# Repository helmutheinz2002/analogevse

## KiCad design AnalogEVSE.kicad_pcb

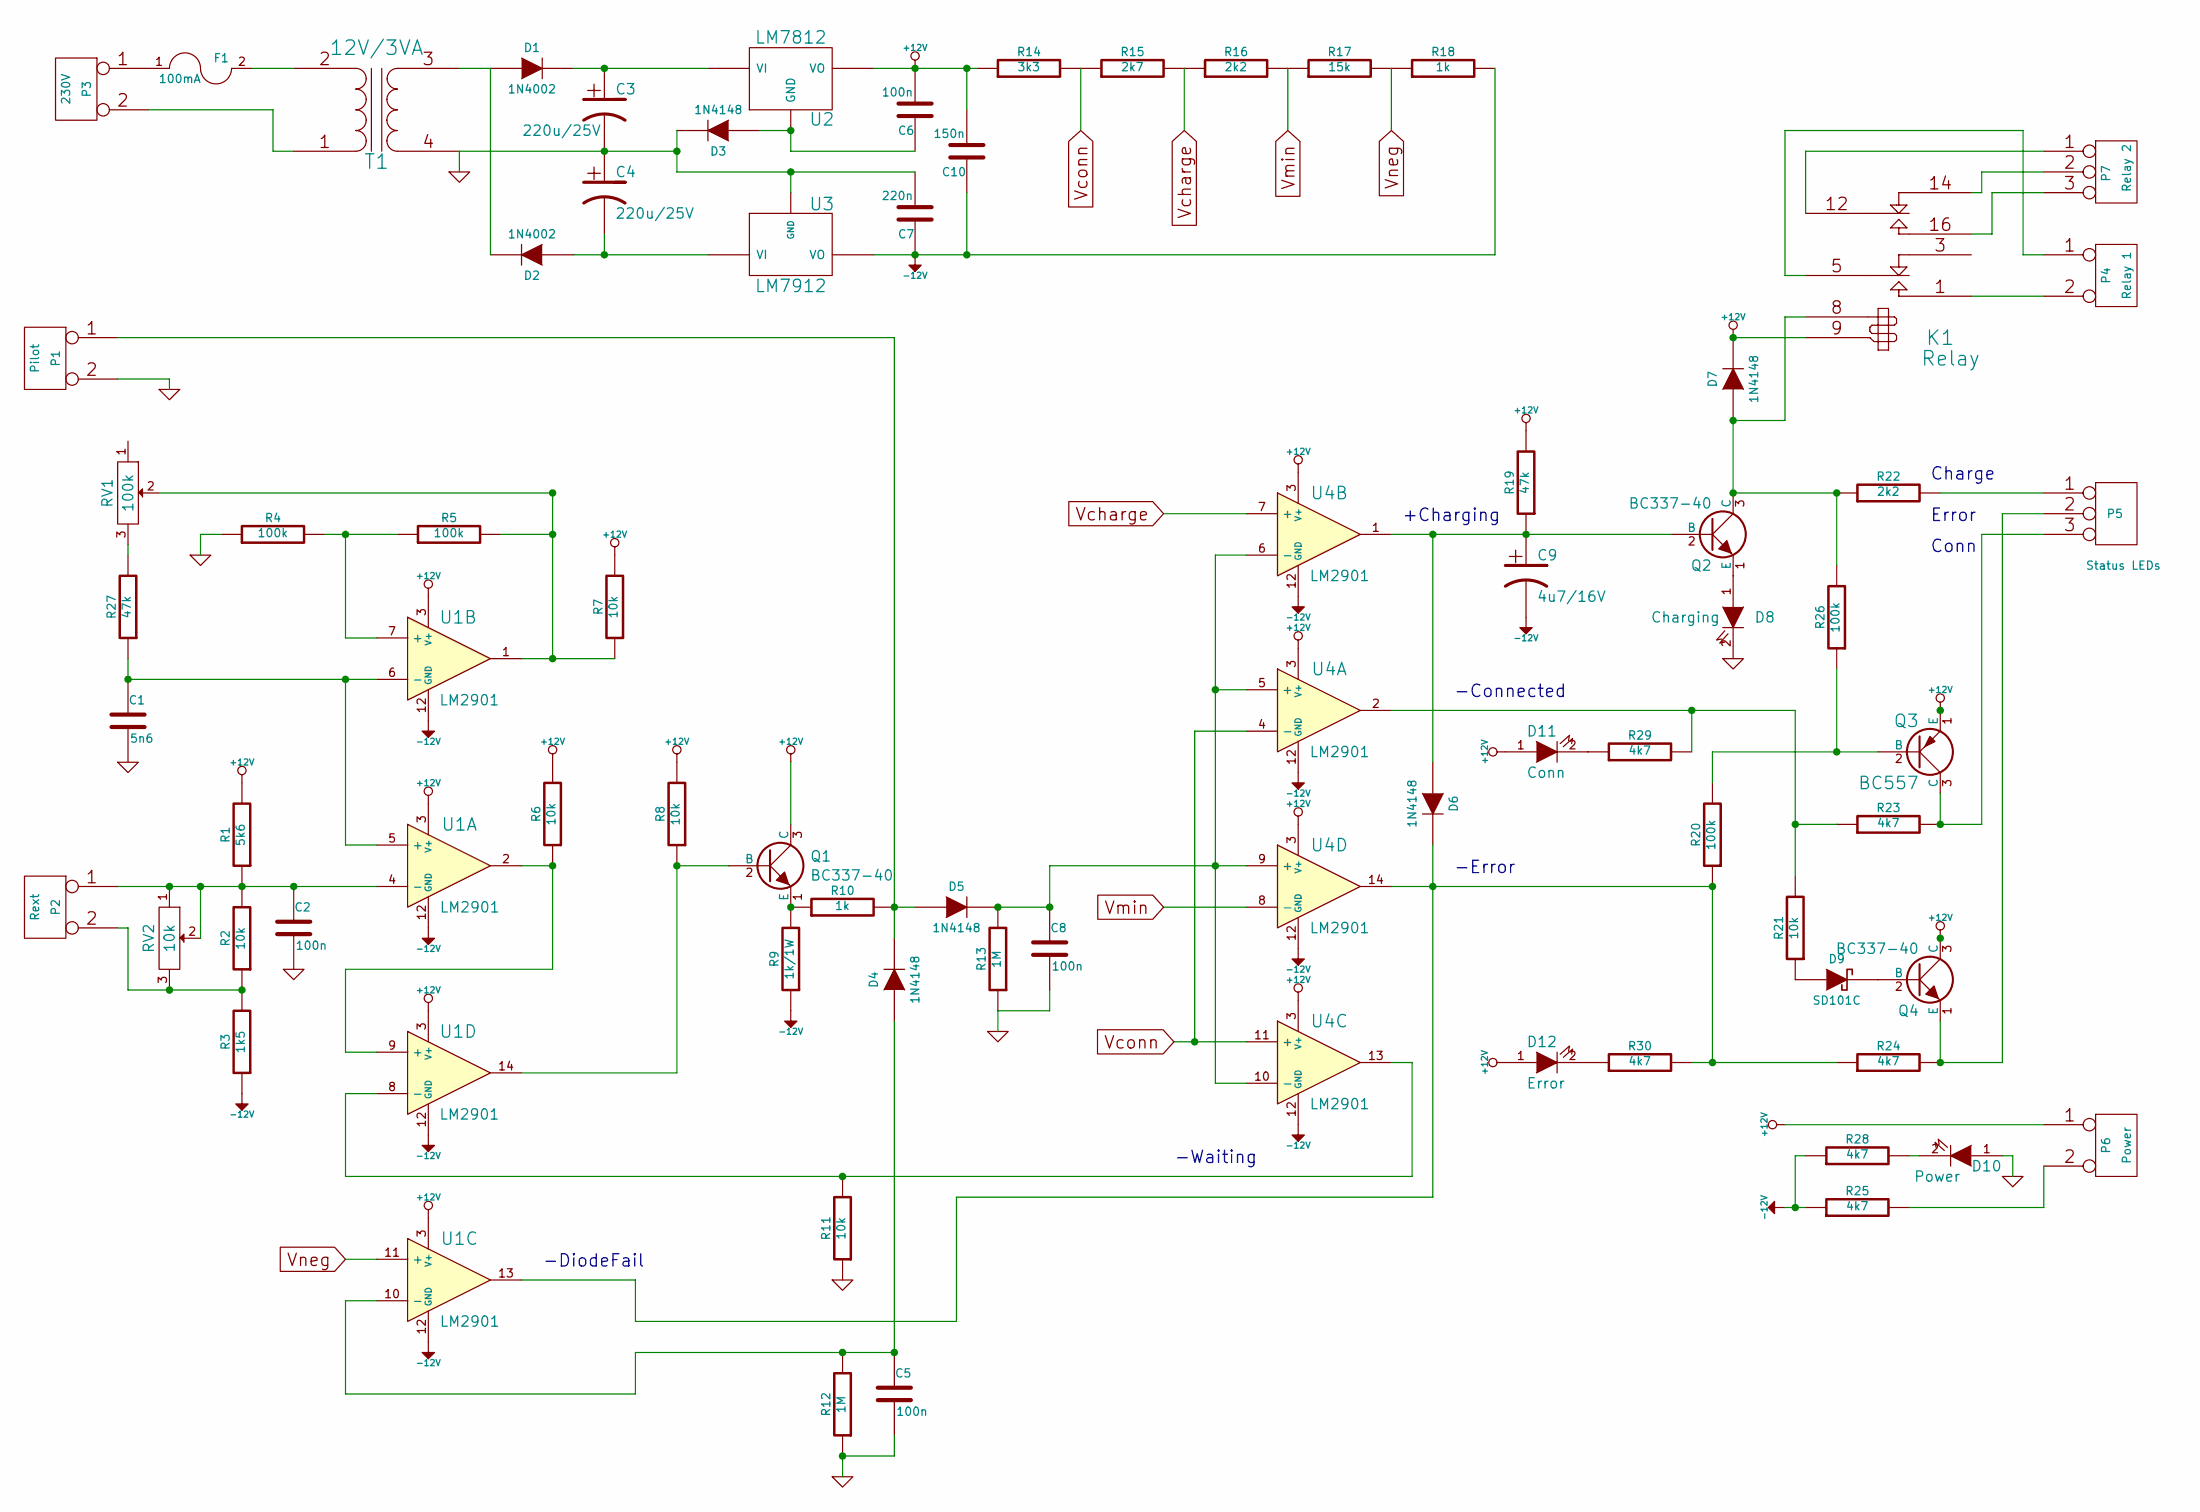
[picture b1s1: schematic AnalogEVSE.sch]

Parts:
C1: 5n6; C2
C2, C5, C6, C8: 100n; C2
C3, C4: 220u/25V; C3
C7: 220n; C2
C9: 4u7/16V; C4
C10: 150n; C2
D1, D2: 1N4002; D3-big
D3, D4, D5, D6, D7: 1N4148; D3
D8: Charging; LED-3
D9: SD101C; D3
D10: Power; LED-3
D11: Conn; LED-3
D12: Error; LED-3
F1: 100mA; Fuse-RM9
K1: Relay
P1: Pilot; Term-2pin
P2: Rext; Term-2pin
P3: 230V; Term-2pin
P4: Relay 1; Term-2pin
P5: Status LEDs; Term-3pin
P6: Power; Term-2pin
P7: Relay 2; Term-3pin
Q1, Q2, Q4: BC337-40; TO92
Q3: BC557; TO92
R1: 5k6; R4-LARGE_PADS
R2, R6, R7, R8, R11, R21: 10k; R4-LARGE_PADS
R3: 1k5; R4-LARGE_PADS
R4, R5, R20, R26: 100k; R4-LARGE_PADS
R9: 1k/1W; R8
R10, R18: 1k; R4-LARGE_PADS
R12, R13: 1M; R4-LARGE_PADS
R14: 3k3; R4-LARGE_PADS
R15: 2k7; R4-LARGE_PADS
R16, R22: 2k2; R4-LARGE_PADS
R17: 15k; R4-LARGE_PADS
R19, R27: 47k; R4-LARGE_PADS
R23, R24, R25, R28, R29, R30: 4k7; R4-LARGE_PADS
RV1: 100k; Trimpot
RV2: 10k; Trimpot2
T1: 12V/3VA; Printtrafo
U1, U4: LM2901; IC-DIP-14
U2: LM7812
U3: LM7912

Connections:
+12V: C6.2, C10.2, D7.2 (K), D11.1 (A), D12.1 (A), K1.9, P6.1, Q1.3 (C), Q3.1 (E), Q4.3 (C), R1.2, R6.2, R7.2, R8.2, R14.1, R19.2, U1.3 (V+), U2.VO, U4.3 (V+)
-12V: C7.1, C9.2, C10.1, R3.1, R9.1, R18.2, R25.1, R28.1, U1.12 (GND), U3.VO, U4.12 (GND)
GND: C1.2, C2.2, C3.2, C4.1, C5.2, C7.2, C8.2, D3.2 (K), D8.2 (K), D10.1 (A), P1.2 (PM), R4.1, R11.1, R12.1, R13.1, T1.4 (SB), U3.GND
unnamed: C1.1, R27.1, U1.5 (+), U1.6 (-)
unnamed: C2.1, P2.1, R1.1, R2.2, RV2.1, RV2.2, U1.4 (-)
unnamed: C3.1, D1.2 (K), U2.VI
unnamed: C4.2, D2.1 (A), U3.VI
unnamed: C5.1, D4.1 (A), R12.2, U1.10 (-)
unnamed: C6.1, D3.1 (A), U2.GND
unnamed: C8.1, D5.2 (K), R13.2, U4.5 (+), U4.6 (-), U4.9 (+), U4.10 (-)
unnamed: C9.1, D6.1 (A), Q2.2 (B), R19.1, U4.1
unnamed: D1.1 (A), D2.2 (K), T1.3 (SA)
unnamed: D4.2 (K), D5.1 (A), P1.1, R10.2
unnamed: D6.2 (K), R20.1, R24.1, R30.2, U1.13, U4.14
unnamed: D7.1 (A), K1.8, Q2.3 (C), R22.1, R26.2
unnamed: D8.1 (A), Q2.1 (E)
unnamed: D9.1 (A), R21.1
unnamed: D9.2 (K), Q4.2 (B)
unnamed: D10.2 (K), R28.2
unnamed: D11.2 (K), R29.1
unnamed: D12.2 (K), R30.1
unnamed: F1.1, P3.1
unnamed: F1.2, T1.2 (AB)
unnamed: K1.1 (T1), P4.2 (PM)
unnamed: K1.5 (C1), P4.1
unnamed: K1.12 (C2), P7.1
unnamed: K1.14 (R2), P7.2 (PM)
unnamed: K1.16 (T2), P7.3
unnamed: P2.2 (PM), R2.1, R3.2, RV2.3
unnamed: P3.2 (PM), T1.1 (AA)
unnamed: P5.1, R22.2
unnamed: P5.2 (PM), Q4.1 (E), R24.2
unnamed: P5.3, Q3.3 (C), R23.2
unnamed: P6.2 (PM), R25.2
unnamed: Q1.1 (E), R9.2, R10.1
unnamed: Q1.2 (B), R8.1, U1.14
unnamed: Q3.2 (B), R20.2, R26.1
unnamed: R4.2, R5.1, U1.7 (+)
unnamed: R5.2, R7.1, RV1.2, U1.1
unnamed: R6.1, U1.2, U1.9 (+)
unnamed: R11.2, U1.8 (-), U4.13
unnamed: R21.2, R23.1, R29.2, U4.2
unnamed: R27.2, RV1.3
Vcharge: R15.2, R16.1, U4.7 (+)
Vconn: R14.2, R15.1, U4.4 (-), U4.11 (+)
Vmin: R16.2, R17.1, U4.8 (-)
Vneg: R17.2, R18.1, U1.11 (+)

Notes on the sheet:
-DiodeFail
+Charging
-Connected
-Error
-Waiting
Conn
Charge
Error

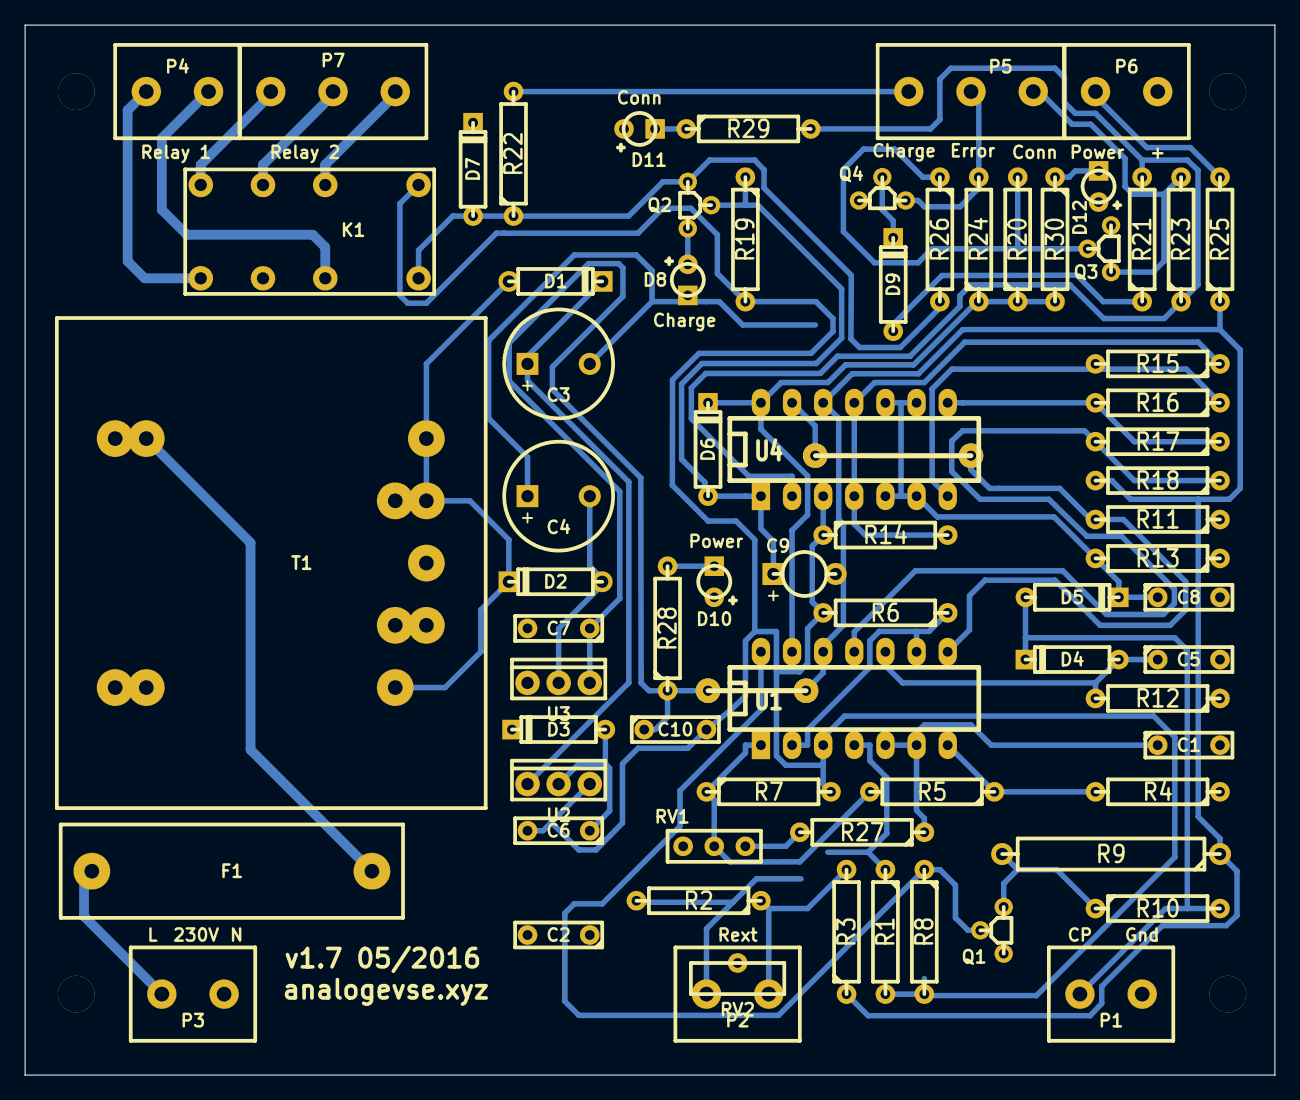
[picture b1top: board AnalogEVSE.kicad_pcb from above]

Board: 2 copper layers, 102.0 x 85.7 mm, 72 parts (0 on the bottom side), 47 nets.

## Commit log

2016-06-01 Added
2016-06-02 Revision
2016-06-05 Filter caps
2016-06-06 Stash
2016-06-06 Library special removed
2016-07-14 Aetzwerk
2016-09-20 Addition of C11
2016-09-20 Lib files added
